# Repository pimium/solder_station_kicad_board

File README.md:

# solder_station_kicad_board
uC board for the solder station

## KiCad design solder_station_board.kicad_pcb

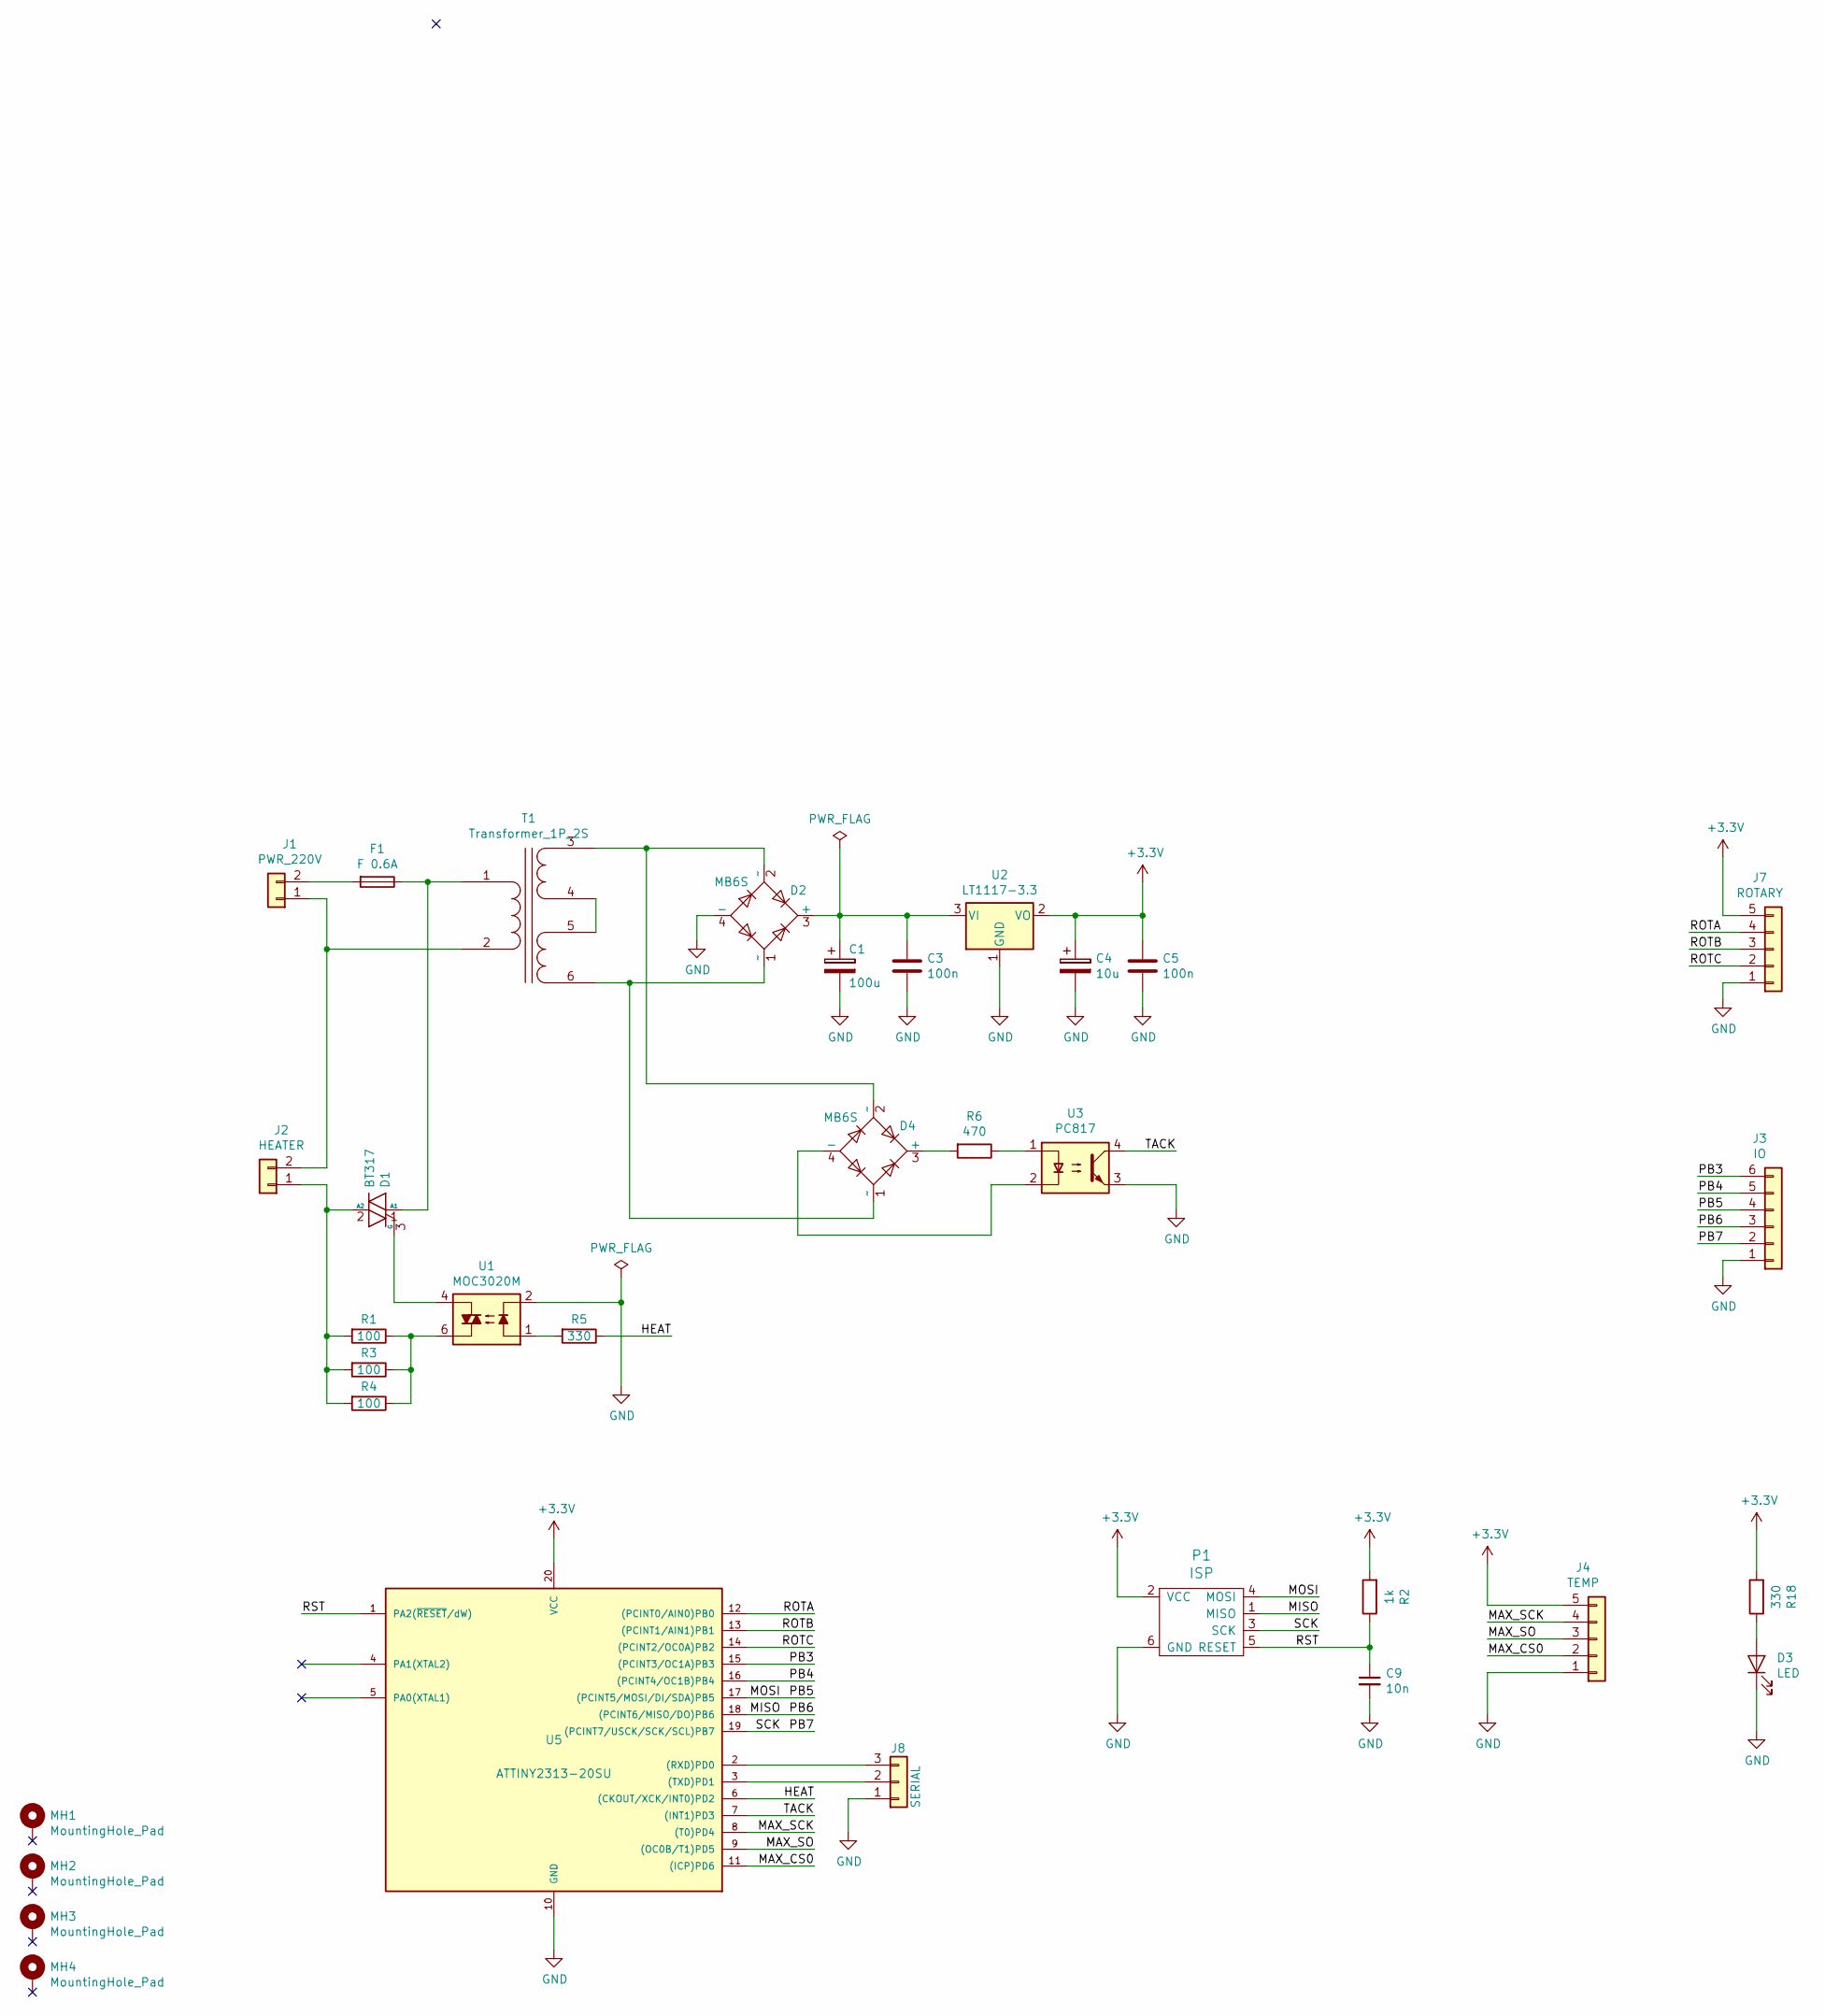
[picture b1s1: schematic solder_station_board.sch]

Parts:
C1: 100u; CP_Radial_D8.0mm_P3.50mm
C3, C5: 100n; C_0805_2012Metric_Pad1.15x1.40mm_HandSolder
C4: 10u; C_2512_6332Metric_Pad1.52x3.35mm_HandSolder
C9: 10n; C_0805_2012Metric_Pad1.15x1.40mm_HandSolder
D1: BT317; TO-126-3_Vertical
D2, D4: MB6S; TO-269AA
D3: LED; LED_D3.0mm
F1: F 0.6A; Fuseholder_Cylinder-5x20mmP1.5_Schurter_0031_8201_Horizonta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
J1: PWR_220V; TerminalBlock_MetzConnect_Type101_RT01602HBWC_1x02_P5.08mm_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
J2: HEATER; TerminalBlock_MetzConnect_Type101_RT01602HBWC_1x02_P5.08mm_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
J3: IO; JST_XH_B6B-XH-A_1x06_P2.50mm_Vertical
J4: TEMP; JST_XH_B5B-XH-A_1x05_P2.50mm_Vertical
J7: ROTARY; PinHeader_1x05_P2.54mm_Vertical
J8: SERIAL; JST_XH_B3B-XH-A_1x03_P2.50mm_Vertical
MH1, MH2, MH3, MH4: MountingHole_Pad; MountingHole_3.2mm_M3_DIN965_Pad
P1: ISP; PinHeader_2x03_P2.54mm_Vertical
R1, R3, R4: 100; R_1206_3216Metric
R2: 1k; R_0603_1608Metric_Pad1.05x0.95mm_HandSolder
R5, R18: 330; R_0603_1608Metric_Pad1.05x0.95mm_HandSolder
R6: 470; R_0603_1608Metric_Pad1.05x0.95mm_HandSolder
T1: Transformer_1P_2S; TRAFO_1P_2S
U1: MOC3020M; DIP-6_W7.62mm_LongPads
U2: LT1117-3.3; SOT-223-3_TabPin2
U3: PC817; DIP-4_W7.62mm
U5: ATTINY2313-20SU; SOIC-20W_7.5x12.8mm_P1.27mm

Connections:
+3V3: C4.1, C5.1, J4.5, J7.5, P1.2 (VCC), R2.2, R18.2, U2.2 (VO), U5.20 (VCC)
/HEAT: R5.1, U5.6 ((CKOUT/XCK/INT0)PD2)
/MAX_CS0: J4.2, U5.11 ((ICP)PD6)
/MAX_SCK: J4.4, U5.8 ((T0)PD4)
/MAX_SO: J4.3, U5.9 ((OC0B/T1)PD5)
/MISO: J3.3, P1.1 (MISO), U5.18 ((PCINT6/MISO/DO)PB6)
/MOSI: J3.4, P1.4 (MOSI), U5.17 ((PCINT5/MOSI/DI/SDA)PB5)
/PB3: J3.6, U5.15 ((PCINT3/OC1A)PB3)
/PB4: J3.5, U5.16 ((PCINT4/OC1B)PB4)
/PB7: J3.2, P1.3 (SCK), U5.19 ((PCINT7/USCK/SCK/SCL)PB7)
/ROTA: J7.4, U5.12 ((PCINT0/AIN0)PB0)
/ROTB: J7.3, U5.13 ((PCINT1/AIN1)PB1)
/ROTC: J7.2, U5.14 ((PCINT2/OC0A)PB2)
/RST: C9.1, P1.5 (RESET), R2.1, U5.1 (PA2(~RESET~/dW))
/TACK: U3.4, U5.7 ((INT1)PD3)
GND: C1.2, C3.2, C4.2, C5.2, C9.2, D2.4 (-), D3.1 (K), J3.1, J4.1, J7.1, J8.1, P1.6 (GND), U1.2, U2.1 (GND), U3.3, U5.10 (GND)
unnamed: C1.1, C3.1, D2.3 (+), U2.3 (VI)
unnamed: D1.1 (A1), F1.1, T1.1 (AA)
unnamed: D1.2 (A2), J2.1, R1.2, R3.2, R4.2
unnamed: D1.3 (G), U1.4
unnamed: D2.1 (~~), D4.1 (~~), T1.6 (SD)
unnamed: D2.2 (~~), D4.2 (~~), T1.3 (SA)
unnamed: D3.2 (A), R18.1
unnamed: D4.3 (+), R6.2
unnamed: D4.4 (-), U3.2
unnamed: F1.2, J1.2
unnamed: J1.1, J2.2, T1.2 (AB)
unnamed: J8.2, U5.3 ((TXD)PD1)
unnamed: J8.3, U5.2 ((RXD)PD0)
unnamed: R1.1, R3.1, R4.1, U1.6
unnamed: R5.2, U1.1
unnamed: R6.1, U3.1
unnamed: T1.4 (SB), T1.5 (SC)

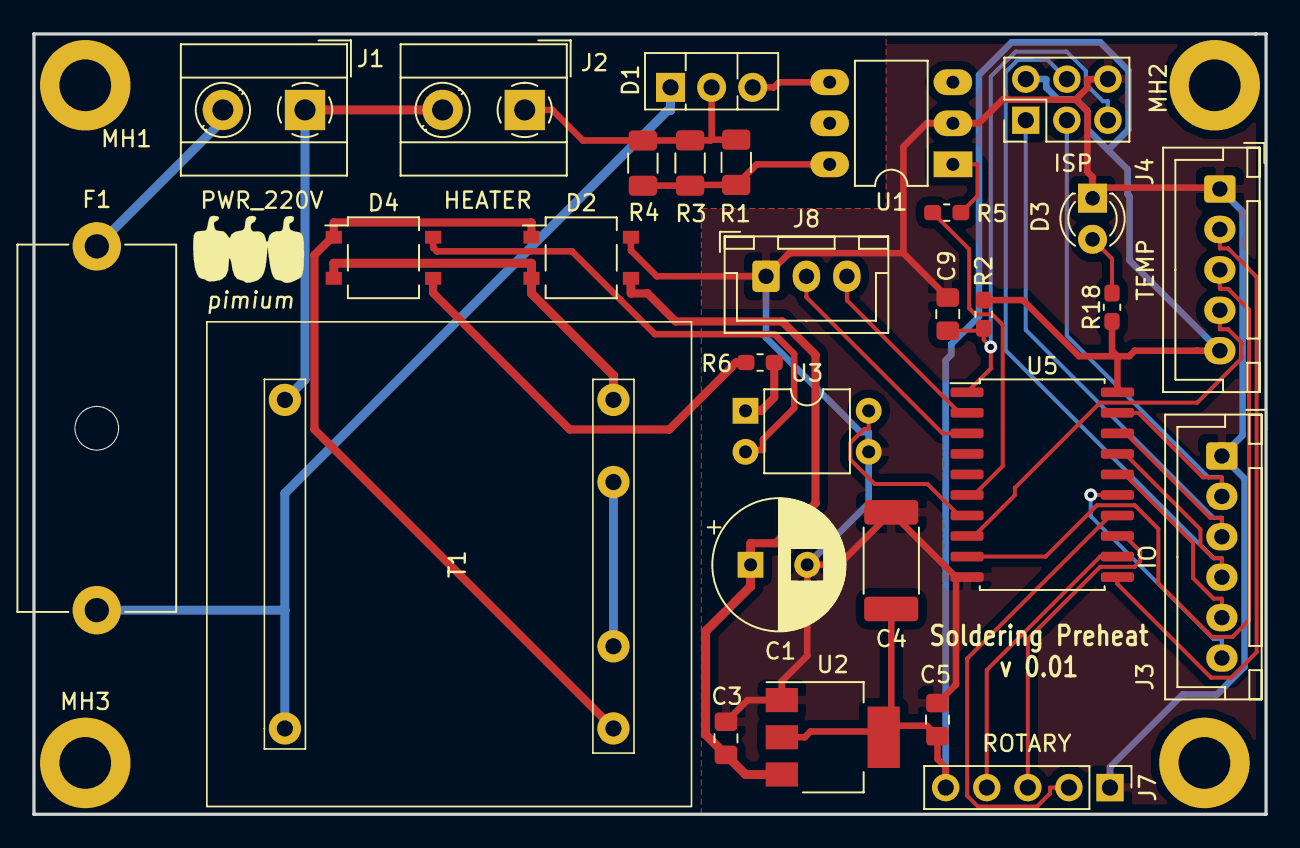
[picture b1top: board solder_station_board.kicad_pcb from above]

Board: 2 copper layers, 76.2 x 48.3 mm, 33 parts (0 on the bottom side), 33 nets.

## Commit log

2018-07-28 remove the power supply from the board
2018-08-18 Save the last working stand
2018-09-29 add attribute file and remove date from pro file
2018-10-13 Add inputs and refine
2018-10-14 Add more inputs
2018-11-18 compensate the delta voltage input with resistors
2018-11-18 Create read me
2018-11-21 add resistor to the + input of opamp
2018-11-25 ready to version
2019-04-13 new board just the adc, atmega and the pnp transistor.
2019-04-13 remove the vfd display and driver from the schematic.
2019-04-27 remove 0R resistors
2020-09-13 small arrangements
2020-10-24 two rt_weller
2020-10-24 v 0.02
2021-02-09 analog done
2021-02-09 remover extra sheet
2021-02-11 place
2021-02-13 change bat to mb6s
